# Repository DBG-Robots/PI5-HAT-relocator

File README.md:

# PI5-HAT-relocator

A simple, shallow KiCad board that lets the Kinematics Kit HAT fit into a narrow robot frame: female connectors on top, male connectors on bottom.

## Background

Our robot uses the **Kinematics Kit** by EduArt Robotik in its Raspberry Pi HAT variant (as in the Eduard robot) as its motor and drive electronics. The same modules are available as the [Kinematics Kit Kim](https://www.eduart-robotik.com/products/kinematicskit-kim), which uses an Ethernet-only board instead of the Pi HAT. In its canonical layout, the motor connectors stick out on the **sides** of the HAT. That is fine for most builds, but it costs width, and width is exactly what we do not have.

## The problem

- **30 cm width limit.** This is the main constraint we are fighting. Everything, including the connectors that stick out of the kit, has to fit inside it.
- **Very shallow frame.** Our double wishbone suspension (3 wheels per side) is mounted on the **sides** of the robot. Most other robots in the league put the suspension *below* the electronics enclosure, which raises the center of mass. We chose the side-mounted layout for a lower center of mass, but it leaves a much narrower and shallower space for the electronics.

## The solution

This board relocates the connectors of the HAT. Rotating the top part of the Kinematics Kit HAT by **90°** brings the motor connectors out of the side-protruding position, so the **entire Kinematics Kit fits fully inside our frame** while staying within the 30 cm width limit and the low profile we need.

*The stack on the Raspberry Pi 5: adapter board at the bottom, the relocator on top of it (the plain board without components), the motor shields rotated by 90° above, power management on top.*

The board is intentionally simple:

- **Female connectors on top** and **male connectors on bottom**, so it sits between the Pi/HAT and the rotated top section.
- No ribbon cable, which keeps the stack low and avoids extra bulk and wiring.
- Silkscreen labels (VCC, GND, EN and signal pairs) on every connector to make assembly and debugging easy.

## Pinout

The board passes through 16 pins (8 two-pin connectors on top, 8 on the bottom). Per motor channel (1 and 2) these are `CH`, `CL`, `EN`, `VCC1`, `VCC2`, plus `GND`.

Only **3 of the 8 connectors** matter electrically: one `VCC`, one `EN` and one CAN connector (`CH`/`CL`). [snaens](https://github.com/snaens) confirmed this to us. `VCC` only carries the Raspberry Pi's current, not motor current: power management sits at the top of the stack and passes motor power down only as far as the motor controllers, not through this board.

We still pass all 16 pins through and populate every connector:

- The pin headers hold the rotated top part in place mechanically. Without them it would not sit firmly.
- The board size is set by the connector positions. With fewer traces it would be neither smaller nor cheaper.
- The board stays usable if more pins are needed later.

Traces: signals 0.2 mm, `VCC` 2.0 mm, `GND` as a pour on both layers.

## Checks

KiCad 10.0.3, as of 2026-11-11:

- **DRC:** no errors, no unconnected pads. Warnings only: silkscreen overlaps, footprints differ from the library, and two vias are stacked at x 117 / y 52 mm (one can be removed).
- **ERC:** no messages.

## Files

| File | Description |
| --- | --- |
| `MotorControllerHeader.kicad_pro` / `.kicad_sch` / `.kicad_pcb` | KiCad project, schematic and PCB layout |
| `PI5-HAT-relocator.step` | 3D model of the assembled board |
| `production/` | Fabrication outputs (BOM, positions, netlist, zip) |
| `SketchPi2PHeaders.dxf` | Mechanical sketch / outline reference |

## Credits

Developed by DBG-Robots, Merlin Ortner (Dietrich-Bonhoeffer-Gymnasium Oberasbach).
Kinematics Kit by EduArt Robotik ([Kinematics Kit Kim](https://www.eduart-robotik.com/products/kinematicskit-kim) is the variant with an Ethernet board).

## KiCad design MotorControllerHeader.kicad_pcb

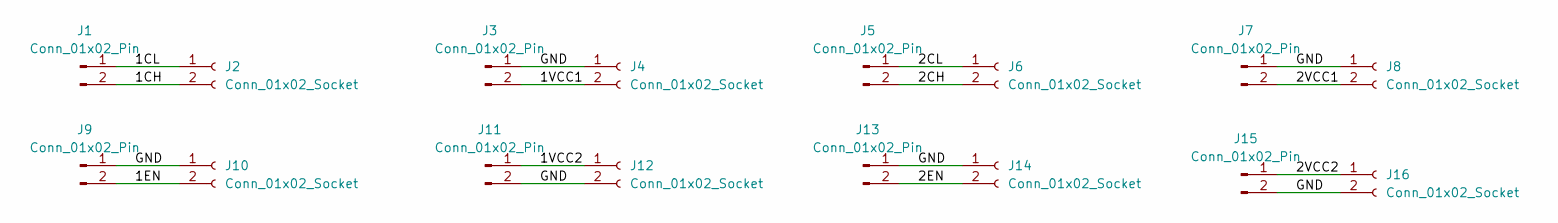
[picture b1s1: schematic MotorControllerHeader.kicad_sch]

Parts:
J1, J3, J5, J7, J9, J11, J13, J15: Conn_01x02_Pin; PinHeader_1x02_P2.54mm_Vertical
J2, J4, J6, J8, J10, J12, J14, J16: Conn_01x02_Socket; PinSocket_1x02_P2.54mm_Vertical

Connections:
/1CH: J1.2, J2.2
/1CL: J1.1, J2.1
/1EN: J9.2, J10.2
/1VCC1: J3.2, J4.2
/1VCC2: J11.1, J12.1
/2CH: J5.2, J6.2
/2CL: J5.1, J6.1
/2EN: J13.2, J14.2
/2VCC1: J7.2, J8.2
/2VCC2: J15.1, J16.1
/GND: J3.1, J4.1, J7.1, J8.1, J9.1, J10.1, J11.2, J12.2, J13.1, J14.1, J15.2, J16.2

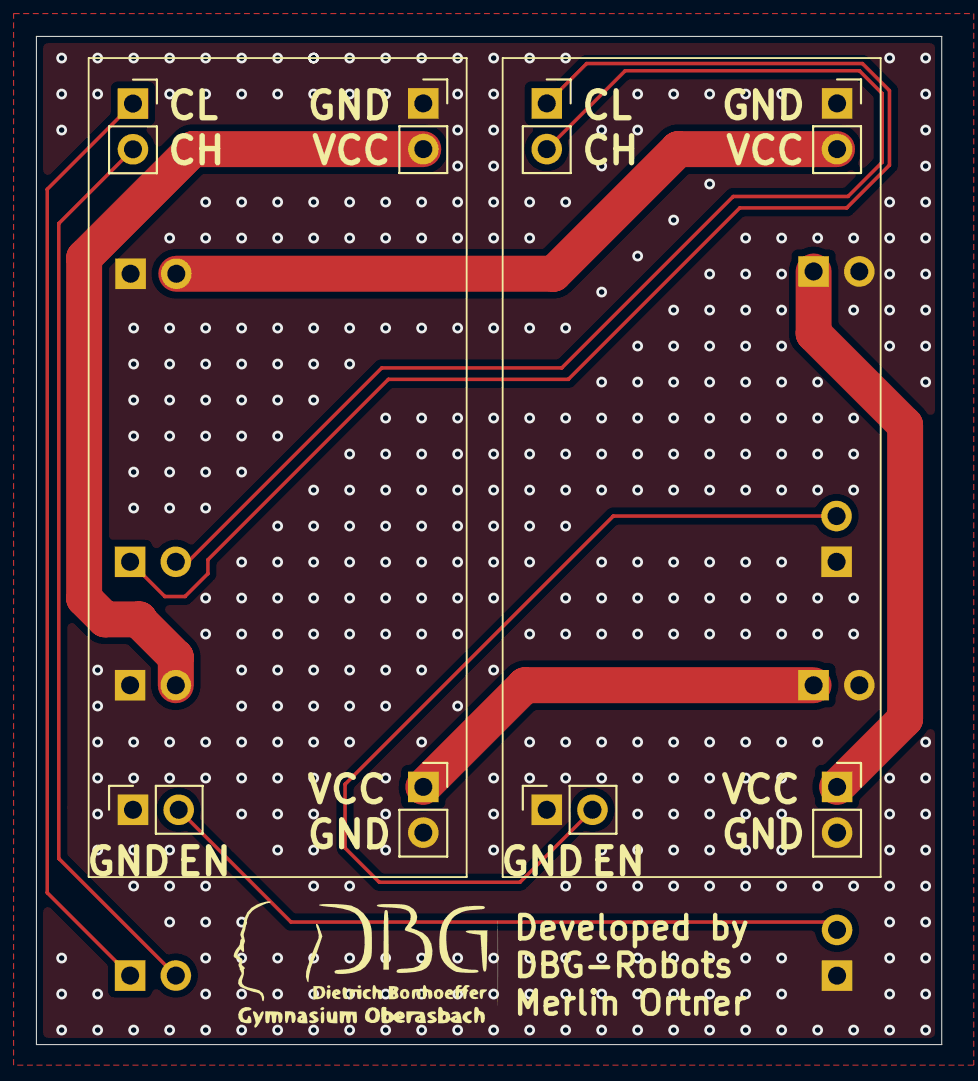
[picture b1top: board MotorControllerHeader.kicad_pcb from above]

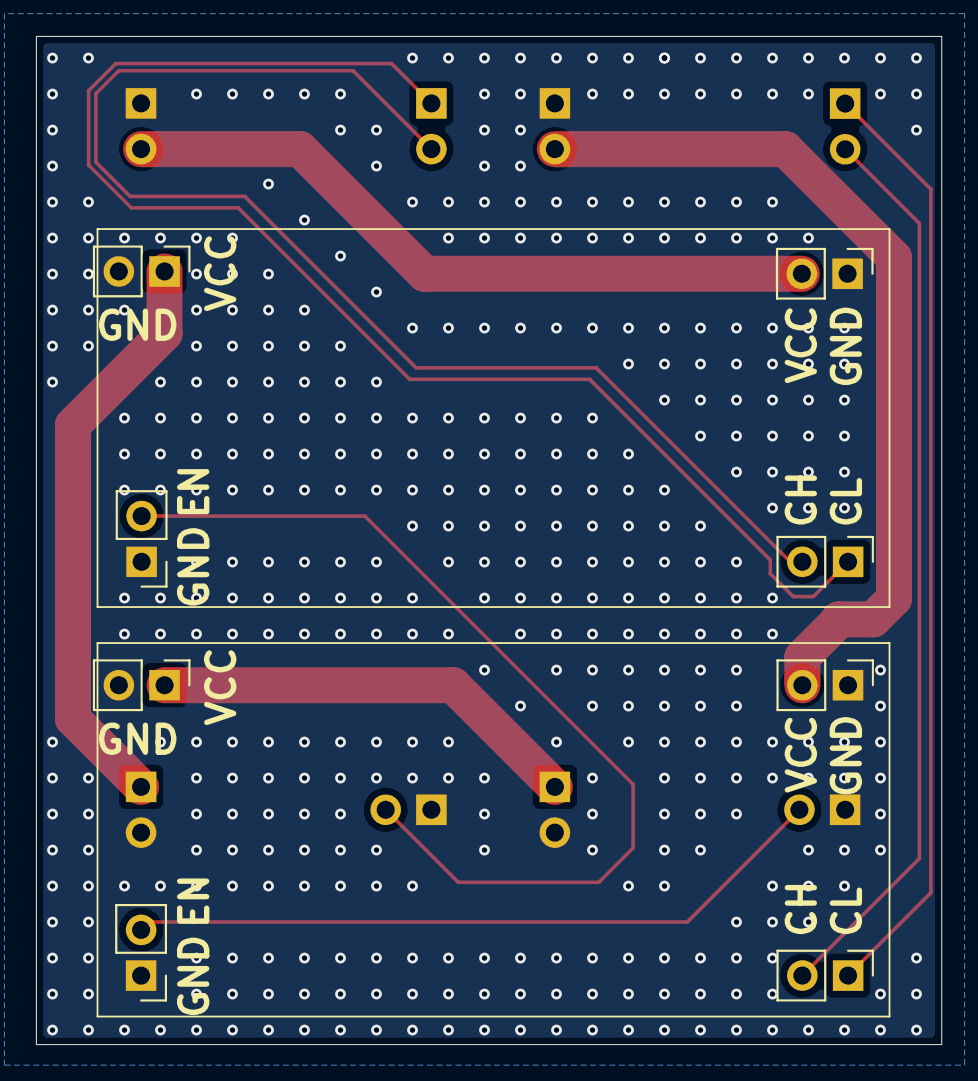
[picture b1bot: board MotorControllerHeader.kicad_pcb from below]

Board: 2 copper layers, 50.3 x 56.0 mm, 16 parts (8 on the bottom side), 11 nets.

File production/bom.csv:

Designator,Footprint,Quantity,Value,LCSC Part #
"J1, J11, J13, J15, J3, J5, J7, J9",PinHeader_1x02_P2.54mm_Vertical,8,Conn_01x02_Pin,
"J10, J12, J14, J16, J2, J4, J6, J8",PinSocket_1x02_P2.54mm_Vertical,8,Conn_01x02_Socket,
